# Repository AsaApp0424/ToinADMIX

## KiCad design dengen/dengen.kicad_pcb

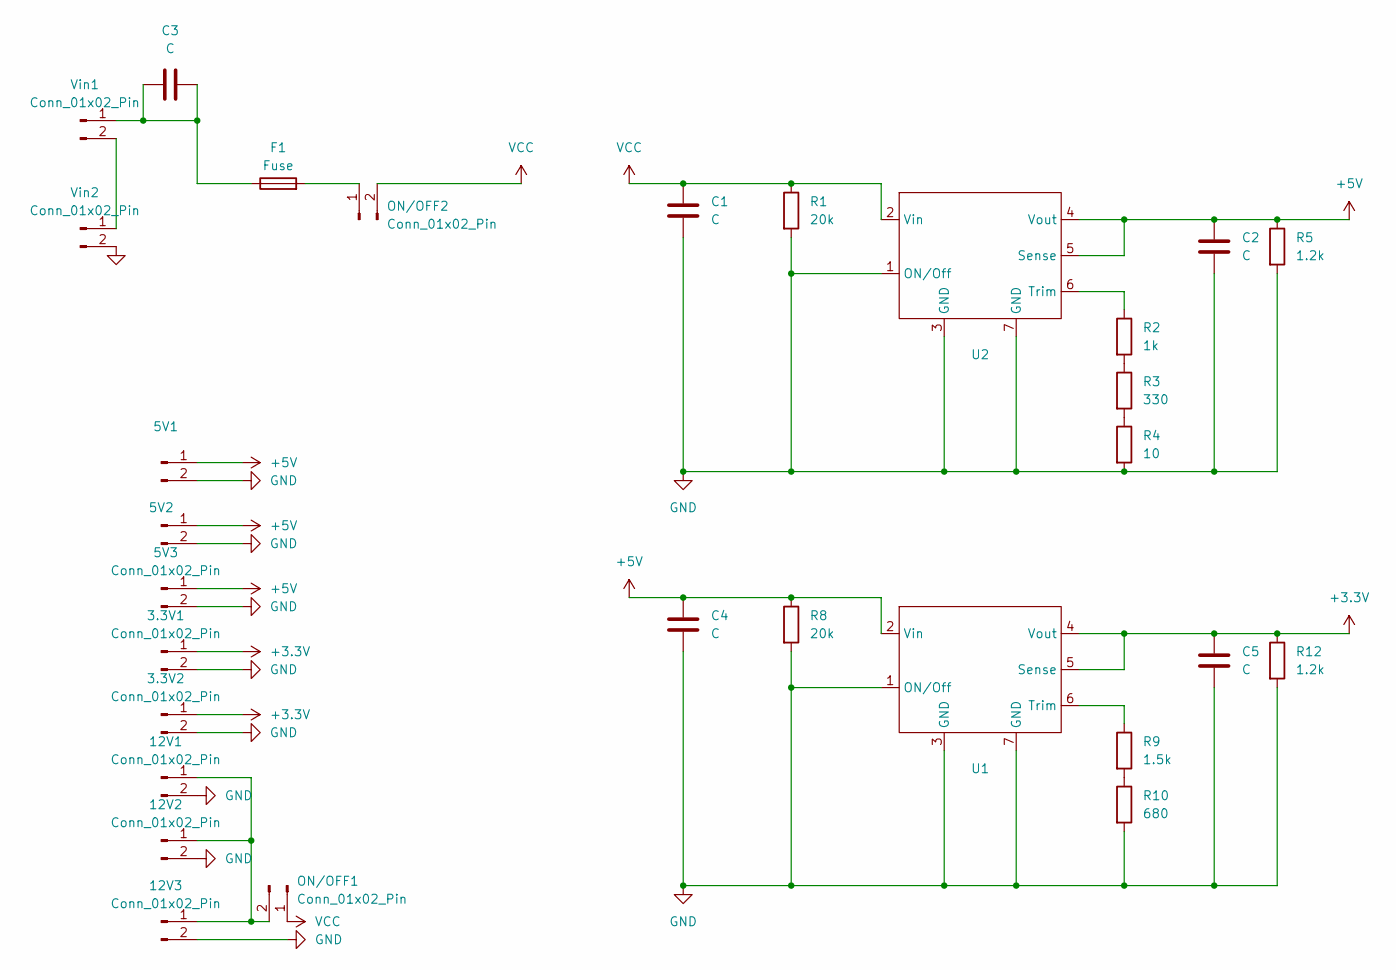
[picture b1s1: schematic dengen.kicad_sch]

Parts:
3.3V1, 3.3V2, 5V1, 5V2, 5V3, 12V1: Conn_01x02_Pin; JST_XH_B2B-XH-A_1x02_P2.50mm_Vertical
12V2, 12V3: Conn_01x02_Pin; JST_XA_S02B-XASK-1N-BN_1x02_P2.50mm_Horizontal
C1, C2, C4, C5: C; C_0805_2012Metric
C3: C
F1: Fuse; fuse clip
ON/OFF1, ON/OFF2: Conn_01x02_Pin; JST_XA_S02B-XASK-1N-BN_1x02_P2.50mm_Horizontal
R1, R8: 20k; R_Axial_DIN0207_L6.3mm_D2.5mm_P7.62mm_Horizontal
R2: 1k; R_Axial_DIN0207_L6.3mm_D2.5mm_P7.62mm_Horizontal
R3: 330; R_Axial_DIN0207_L6.3mm_D2.5mm_P7.62mm_Horizontal
R4: 10; R_Axial_DIN0207_L6.3mm_D2.5mm_P7.62mm_Horizontal
R5, R12: 1.2k; R_Axial_DIN0207_L6.3mm_D2.5mm_P7.62mm_Horizontal
R9: 1.5k; R_Axial_DIN0207_L6.3mm_D2.5mm_P7.62mm_Horizontal
R10: 680; R_Axial_DIN0207_L6.3mm_D2.5mm_P7.62mm_Horizontal
U1, U2: dcdc
Vin1, Vin2: Conn_01x02_Pin; JST_XA_S02B-XASK-1N-BN_1x02_P2.50mm_Horizontal

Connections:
+3.3V: 3.3V1.1, 3.3V2.1, C5.1, R12.1, U1.4 (Vout), U1.5 (Sense)
+5V: 5V1.1, 5V2.1, 5V3.1, C2.1, C4.1, R5.1, R8.1, U1.2 (Vin), U2.4 (Vout), U2.5 (Sense)
GND: 3.3V1.2, 3.3V2.2, 5V1.2, 5V2.2, 5V3.2, 12V1.2, 12V2.2, 12V3.2, C1.2, C2.2, C4.2, C5.2, R1.2, R4.2, R5.2, R8.2, R10.2, R12.2, U1.1 (ON/Off), U1.3 (GND), U1.7 (GND), U2.1 (ON/Off), U2.3 (GND), U2.7 (GND), Vin2.2
unnamed: 12V1.1, 12V2.1, 12V3.1, ON/OFF1.2
unnamed: F1.2, ON/OFF2.1
unnamed: R2.2, R3.1
unnamed: R3.2, R4.1
unnamed: R9.2, R10.1
unnamed: R9.1, U1.6 (Trim)
unnamed: R2.1, U2.6 (Trim)
unnamed: C3.1, C3.2, F1.1, Vin1.1
unnamed: Vin1.2, Vin2.1
VCC: C1.1, ON/OFF1.1, ON/OFF2.2, R1.1, U2.2 (Vin)

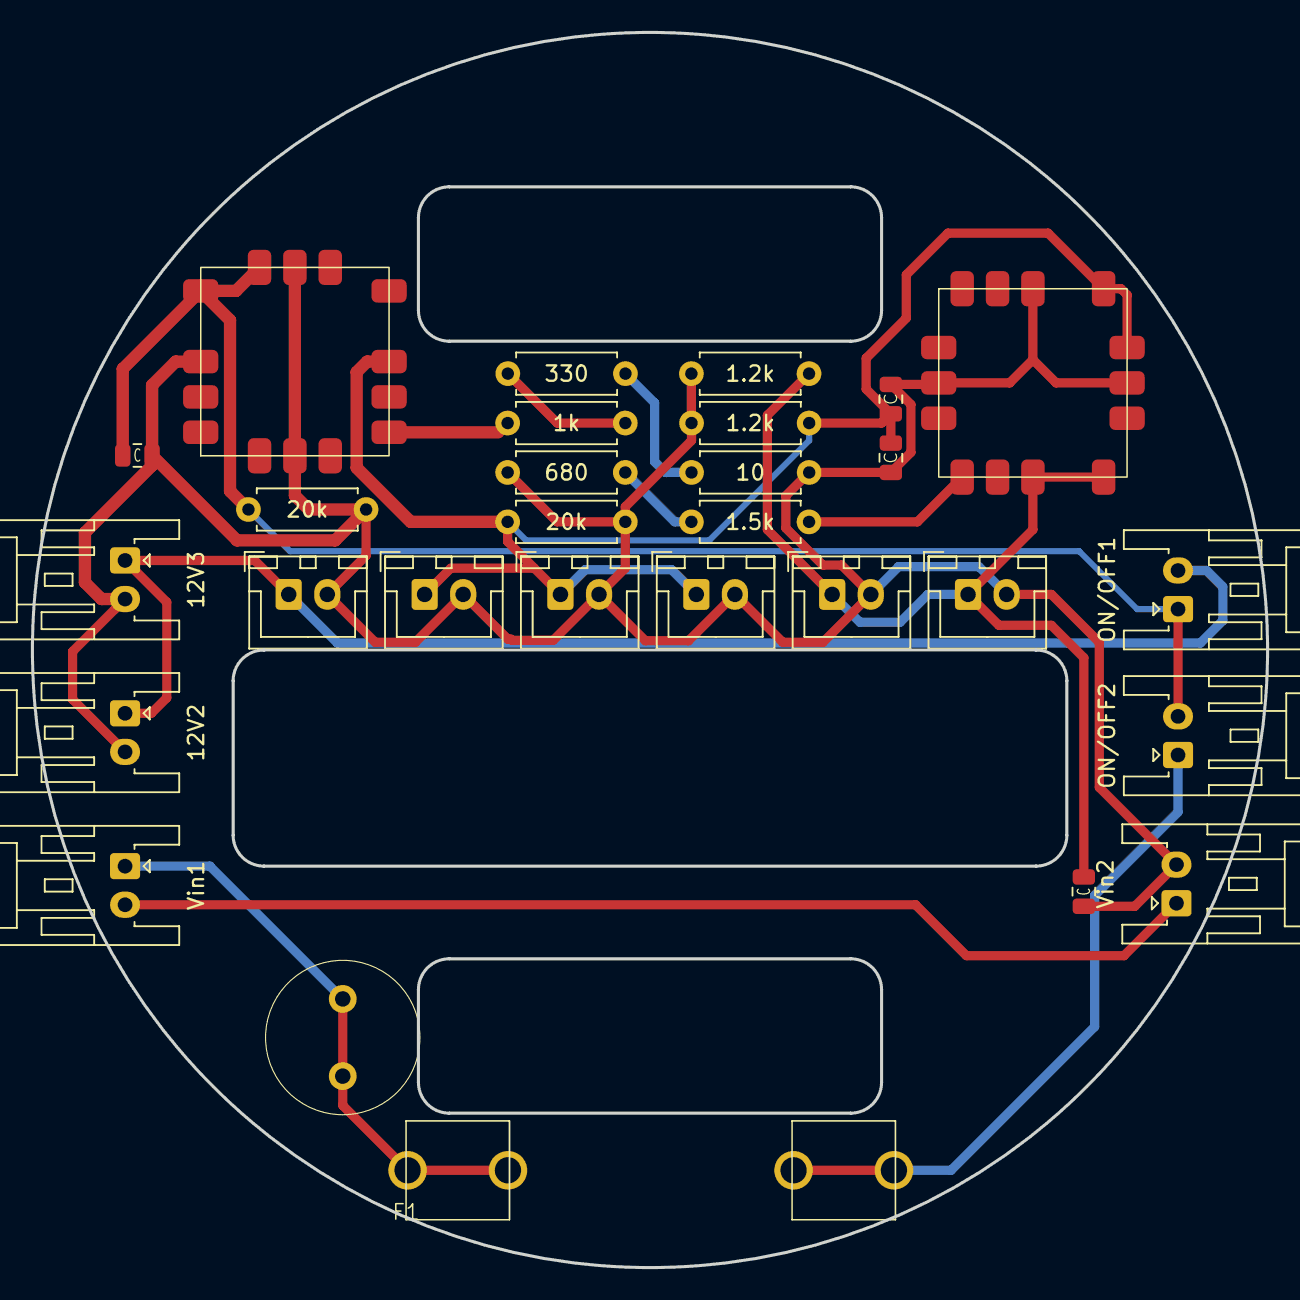
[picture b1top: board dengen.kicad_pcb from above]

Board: 2 copper layers, 80.0 x 80.0 mm, 29 parts (0 on the bottom side), 13 nets.

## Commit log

2024-04-15 test
2024-04-15 Adding Files
2024-04-15 teensy symbol
2024-04-15 tssp58038
2024-04-16 ボルセンローパスフィルター
2024-04-16 display-main接続
2024-04-19 いろいろ
2024-04-20 直接アップロード
